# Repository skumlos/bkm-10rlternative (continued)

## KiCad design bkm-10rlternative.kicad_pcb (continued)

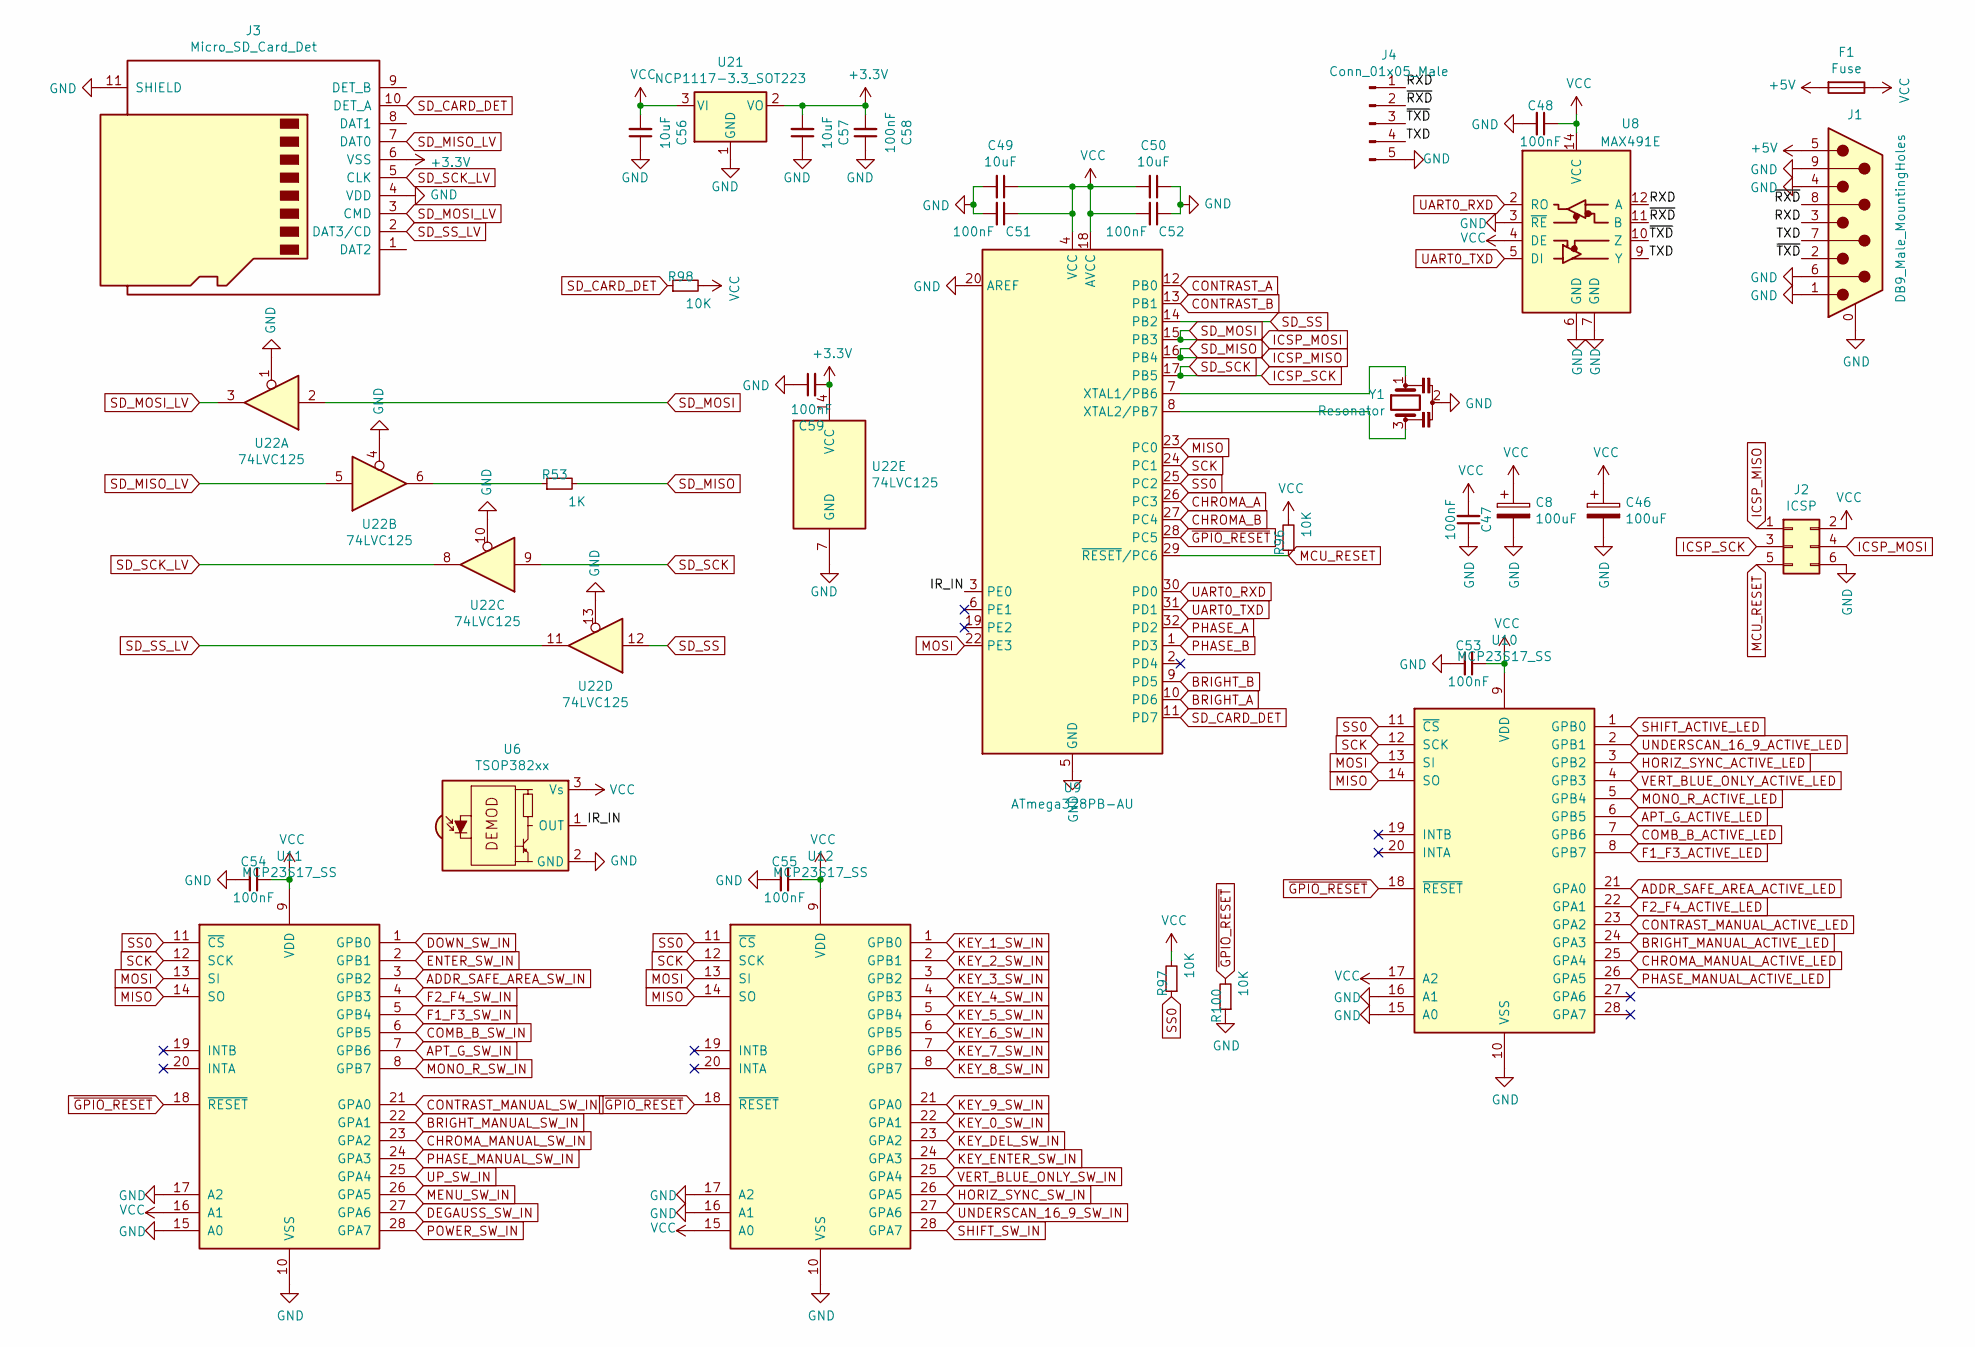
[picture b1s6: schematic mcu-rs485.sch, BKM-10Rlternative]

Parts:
C8, C46: 100uF; CP_Elec_6.3x5.4
C47, C48, C51, C52, C53, C54, C55, C58, C59: 100nF; C_0603_1608Metric_Pad1.08x0.95mm_HandSolder
C49, C50, C56, C57: 10uF; C_0805_2012Metric_Pad1.18x1.45mm_HandSolder
F1: Fuse; Fuse_1206_3216Metric_Pad1.42x1.75mm_HandSolder
J1: DB9_Male_MountingHoles; DSUB-9_Female_Horizontal_P2.77x2.84mm_EdgePinOffset7.70mm_H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
J2: ICSP; PinHeader_2x03_P2.54mm_Vertical
J3: Micro_SD_Card_Det; MEM2061
J4: Conn_01x05_Male; PinHeader_1x05_P2.54mm_Vertical
R53: 1K; R_0603_1608Metric_Pad0.98x0.95mm_HandSolder
R96, R97, R98, R100: 10K; R_0603_1608Metric_Pad0.98x0.95mm_HandSolder
U6: TSOP382xx; Vishay_MINICAST-3Pin
U8: MAX491E; SOIC-14_3.9x8.7mm_P1.27mm
U9: ATmega328PB-AU; TQFP-32_7x7mm_P0.8mm
U10, U11, U12: MCP23S17_SS; SSOP-28_5.3x10.2mm_P0.65mm
U21: NCP1117-3.3_SOT223; SOT-223-3_TabPin2
U22: 74LVC125; TSSOP-14_4.4x5mm_P0.65mm
Y1: Resonator; Resonator_SMD_muRata_CSTxExxV-3Pin_3.0x1.1mm_HandSoldering

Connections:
+3V3: C57.2, C58.2, C59.2, J3.6 (VSS), U21.2 (VO), U22.14 (VCC)
+5V: F1.2, J1.5
/MCU+RS485/IR_IN: U6.1 (OUT), U9.3 (PE0)
/MCU+RS485/RXD: J1.3, J4.1, U8.12 (A)
/MCU+RS485/TXD: J1.7, J4.4, U8.9 (Y)
/MCU+RS485/~RXD: J1.8, J4.2, U8.11 (B)
/MCU+RS485/~TXD: J1.2, J4.3, U8.10 (Z)
ADDR_SAFE_AREA_ACTIVE_LED: U10.21 (GPA0); also elsewhere on the board
ADDR_SAFE_AREA_SW_IN: U11.3 (GPB2); also elsewhere on the board
APT_G_ACTIVE_LED: U10.6 (GPB5); also elsewhere on the board
APT_G_SW_IN: U11.7 (GPB6); also elsewhere on the board
BRIGHT_A: U9.10 (PD6); also elsewhere on the board
BRIGHT_B: U9.9 (PD5); also elsewhere on the board
BRIGHT_MANUAL_ACTIVE_LED: U10.24 (GPA3); also elsewhere on the board
BRIGHT_MANUAL_SW_IN: U11.22 (GPA1); also elsewhere on the board
CHROMA_A: U9.26 (PC3); also elsewhere on the board
CHROMA_B: U9.27 (PC4); also elsewhere on the board
CHROMA_MANUAL_ACTIVE_LED: U10.25 (GPA4); also elsewhere on the board
CHROMA_MANUAL_SW_IN: U11.23 (GPA2); also elsewhere on the board
COMB_B_ACTIVE_LED: U10.7 (GPB6); also elsewhere on the board
COMB_B_SW_IN: U11.6 (GPB5); also elsewhere on the board
CONTRAST_A: U9.12 (PB0); also elsewhere on the board
CONTRAST_B: U9.13 (PB1); also elsewhere on the board
CONTRAST_MANUAL_ACTIVE_LED: U10.23 (GPA2); also elsewhere on the board
CONTRAST_MANUAL_SW_IN: U11.21 (GPA0); also elsewhere on the board
DEGAUSS_SW_IN: U11.27 (GPA6); also elsewhere on the board
DOWN_SW_IN: U11.1 (GPB0); also elsewhere on the board
ENTER_SW_IN: U11.2 (GPB1); also elsewhere on the board
F1_F3_ACTIVE_LED: U10.8 (GPB7); also elsewhere on the board
F1_F3_SW_IN: U11.5 (GPB4); also elsewhere on the board
F2_F4_ACTIVE_LED: U10.22 (GPA1); also elsewhere on the board
F2_F4_SW_IN: U11.4 (GPB3); also elsewhere on the board
GND: C8.2, C46.2, C47.1, C48.2, C49.2, C50.1, C51.2, C52.1, C53.2, C54.2, C55.2, C56.1, C57.1, C58.1, C59.1, J1.0 (PAD), J1.1, J1.4, J1.6, J1.9, J2.6, J3.4 (VDD), J3.11 (SHIELD), J4.5, R100.1, U6.2 (GND), U8.3 (~RE), U8.6 (GND), U8.7 (GND), U9.5 (GND), U9.20 (AREF), U9.21 (GND), U10.10 (VSS), U10.15 (A0), U10.16 (A1), U11.10 (VSS), U11.15 (A0), U11.17 (A2), U12.10 (VSS), U12.16 (A1), U12.17 (A2), U21.1 (GND), U22.1, U22.4, U22.7 (GND), U22.10, U22.13, Y1.2; also elsewhere on the board
HORIZ_SYNC_ACTIVE_LED: U10.3 (GPB2); also elsewhere on the board
HORIZ_SYNC_SW_IN: U12.26 (GPA5); also elsewhere on the board
ICSP_MISO: J2.1, R53.2, U9.16 (PB4)
ICSP_MOSI: J2.4, U9.15 (PB3), U22.2
ICSP_SCK: J2.3, U9.17 (PB5), U22.9
KEY_0_SW_IN: U12.22 (GPA1); also elsewhere on the board
KEY_1_SW_IN: U12.1 (GPB0); also elsewhere on the board
KEY_2_SW_IN: U12.2 (GPB1); also elsewhere on the board
KEY_3_SW_IN: U12.3 (GPB2); also elsewhere on the board
KEY_4_SW_IN: U12.4 (GPB3); also elsewhere on the board
KEY_5_SW_IN: U12.5 (GPB4); also elsewhere on the board
KEY_6_SW_IN: U12.6 (GPB5); also elsewhere on the board
KEY_7_SW_IN: U12.7 (GPB6); also elsewhere on the board
KEY_8_SW_IN: U12.8 (GPB7); also elsewhere on the board
KEY_9_SW_IN: U12.21 (GPA0); also elsewhere on the board
KEY_DEL_SW_IN: U12.23 (GPA2); also elsewhere on the board
KEY_ENTER_SW_IN: U12.24 (GPA3); also elsewhere on the board
MCU_RESET: J2.5, R96.1, U9.29 (~RESET~/PC6)
MENU_SW_IN: U11.26 (GPA5); also elsewhere on the board
MISO: U9.23 (PC0), U10.14 (SO), U11.14 (SO), U12.14 (SO)
MONO_R_ACTIVE_LED: U10.5 (GPB4); also elsewhere on the board
MONO_R_SW_IN: U11.8 (GPB7); also elsewhere on the board
MOSI: U9.22 (PE3), U10.13 (SI), U11.13 (SI), U12.13 (SI)
unnamed: R53.1, U22.6
unnamed: U9.7 (XTAL1/PB6), Y1.1
unnamed: U9.8 (XTAL2/PB7), Y1.3
PHASE_A: U9.32 (PD2); also elsewhere on the board
PHASE_B: U9.1 (PD3); also elsewhere on the board
PHASE_MANUAL_ACTIVE_LED: U10.26 (GPA5); also elsewhere on the board
PHASE_MANUAL_SW_IN: U11.24 (GPA3); also elsewhere on the board
POWER_SW_IN: U11.28 (GPA7); also elsewhere on the board
SCK: U9.24 (PC1), U10.12 (SCK), U11.12 (SCK), U12.12 (SCK)
SD_CARD_DET: J3.10 (DET_A), R98.1, U9.11 (PD7)
SD_MISO_LV: J3.7 (DAT0), U22.5
SD_MOSI_LV: J3.3 (CMD), U22.3
SD_SCK_LV: J3.5 (CLK), U22.8
SD_SS: U9.14 (PB2), U22.12
SD_SS_LV: J3.2 (DAT3/CD), U22.11
SHIFT_ACTIVE_LED: U10.1 (GPB0); also elsewhere on the board
SHIFT_SW_IN: U12.28 (GPA7); also elsewhere on the board
SS0: R97.1, U9.25 (PC2), U10.11 (~CS~), U11.11 (~CS~), U12.11 (~CS~)
UART0_RXD: U8.2 (RO), U9.30 (PD0)
UART0_TXD: U8.5 (DI), U9.31 (PD1)
UNDERSCAN_16_9_ACTIVE_LED: U10.2 (GPB1); also elsewhere on the board
UNDERSCAN_16_9_SW_IN: U12.27 (GPA6); also elsewhere on the board
UP_SW_IN: U11.25 (GPA4); also elsewhere on the board
VCC: C8.1, C46.1, C47.2, C48.1, C49.1, C50.2, C51.1, C52.2, C53.1, C54.1, C55.1, C56.2, F1.1, J2.2, R96.2, R97.2, R98.2, U6.3 (Vs), U8.4 (DE), U8.14 (VCC), U9.4 (VCC), U9.18 (AVCC), U10.9 (VDD), U10.17 (A2), U11.9 (VDD), U11.16 (A1), U12.9 (VDD), U12.15 (A0), U21.3 (VI); also elsewhere on the board
VERT_BLUE_ONLY_ACTIVE_LED: U10.4 (GPB3); also elsewhere on the board
VERT_BLUE_ONLY_SW_IN: U12.25 (GPA4); also elsewhere on the board
~GPIO_RESET: R100.2, U9.28 (PC5), U10.18 (~RESET~), U11.18 (~RESET~), U12.18 (~RESET~)

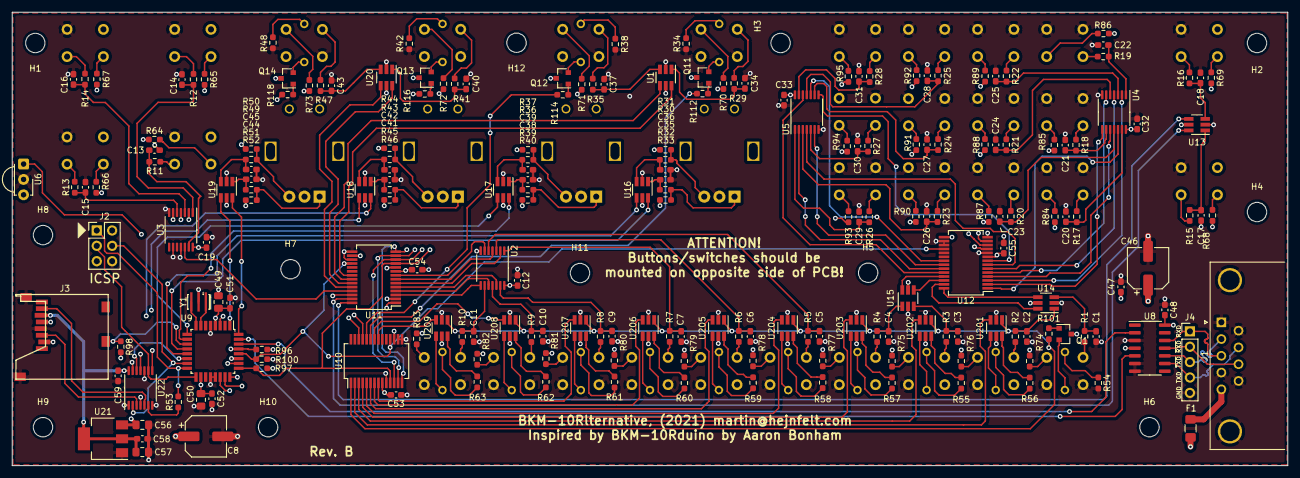
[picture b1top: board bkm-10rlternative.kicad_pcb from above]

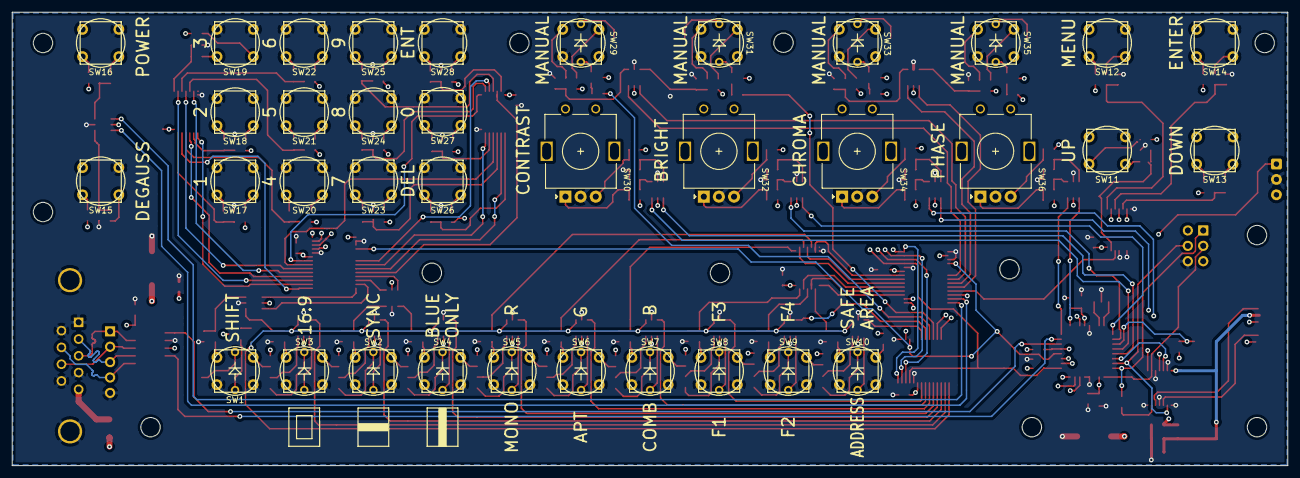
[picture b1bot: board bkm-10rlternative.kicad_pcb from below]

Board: 4 copper layers, 210.8 x 74.9 mm, 252 parts (36 on the bottom side), 237 nets.

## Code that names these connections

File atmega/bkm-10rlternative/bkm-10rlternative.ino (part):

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#include "ButtonDefs.h"

// Direct IOs
#define GPIO_RESET        (A5)

#define CONTRAST_A        (8)
#define CONTRAST_B        (9)
#define BRIGHT_A          (10)
#define BRIGHT_B          (11)
#define CHROMA_A          (12)
#define CHROMA_B          (13)
#define PHASE_A           (24)
#define PHASE_B           (25)

#define U11_SS            (A4)
#define U12_SS            (A3)
#define U10_SS            (A2)
#define UART_RTS          (PD2)
#define UART_CTS          (PD3)

#define MENU_IN           (PD5)
#define ENTER_IN          (PD6)
#define UP_IN             (PD4)
#define DOWN_IN           (PD7)

// U11
#define CONTRAST_MANUAL (0x0001)
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#define ENCODER_COUNT (4)

Encoder encoders[ENCODER_COUNT] = {
  { .m_value = 0, .m_id = ENCODER_CONTRAST, .m_pinA = CONTRAST_A, .m_pinB = CONTRAST_B  },
  { .m_value = 0, .m_id = ENCODER_BRIGHT,   .m_pinA = BRIGHT_A,   .m_pinB = BRIGHT_B    },
  { .m_value = 0, .m_id = ENCODER_CHROMA,   .m_pinA = CHROMA_A,   .m_pinB = CHROMA_B    },
  { .m_value = 0, .m_id = ENCODER_PHASE,    .m_pinA = PHASE_A,    .m_pinB = PHASE_B     }
};

void rotaryEncoderChanged(void* encoder, bool pinstate) {
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
void setup() {
  Serial.begin(38400);
  pinMode(GPIO_RESET, OUTPUT);
  pinMode(UART_RTS, OUTPUT);
  pinMode(UART_CTS, OUTPUT);
  
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  pinMode(UP_IN, INPUT);
  pinMode(DOWN_IN, INPUT);
  
  digitalWrite(GPIO_RESET, HIGH);
  digitalWrite(UART_RTS, HIGH);
  digitalWrite(UART_CTS, LOW);
  delay(100);
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
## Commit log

2021-11-04 Initial PCB routed
2021-11-05 Added texts, fixed pullups
2021-11-05 Minor changes
2021-12-13 A bunch of changes, full duplex 422
2022-01-05 Fixed switch footprints and encoder resistors
2022-01-05 Added MCU code
2022-01-05 Readme
2022-01-08 Update atmega readme
2022-01-08 3D files and minor stuff
2022-01-08 Update README yet again
2022-01-08 Updated readme with serial cable info
2022-01-11 Updated readme agaaaaain...
2022-04-14 Initial revision B
